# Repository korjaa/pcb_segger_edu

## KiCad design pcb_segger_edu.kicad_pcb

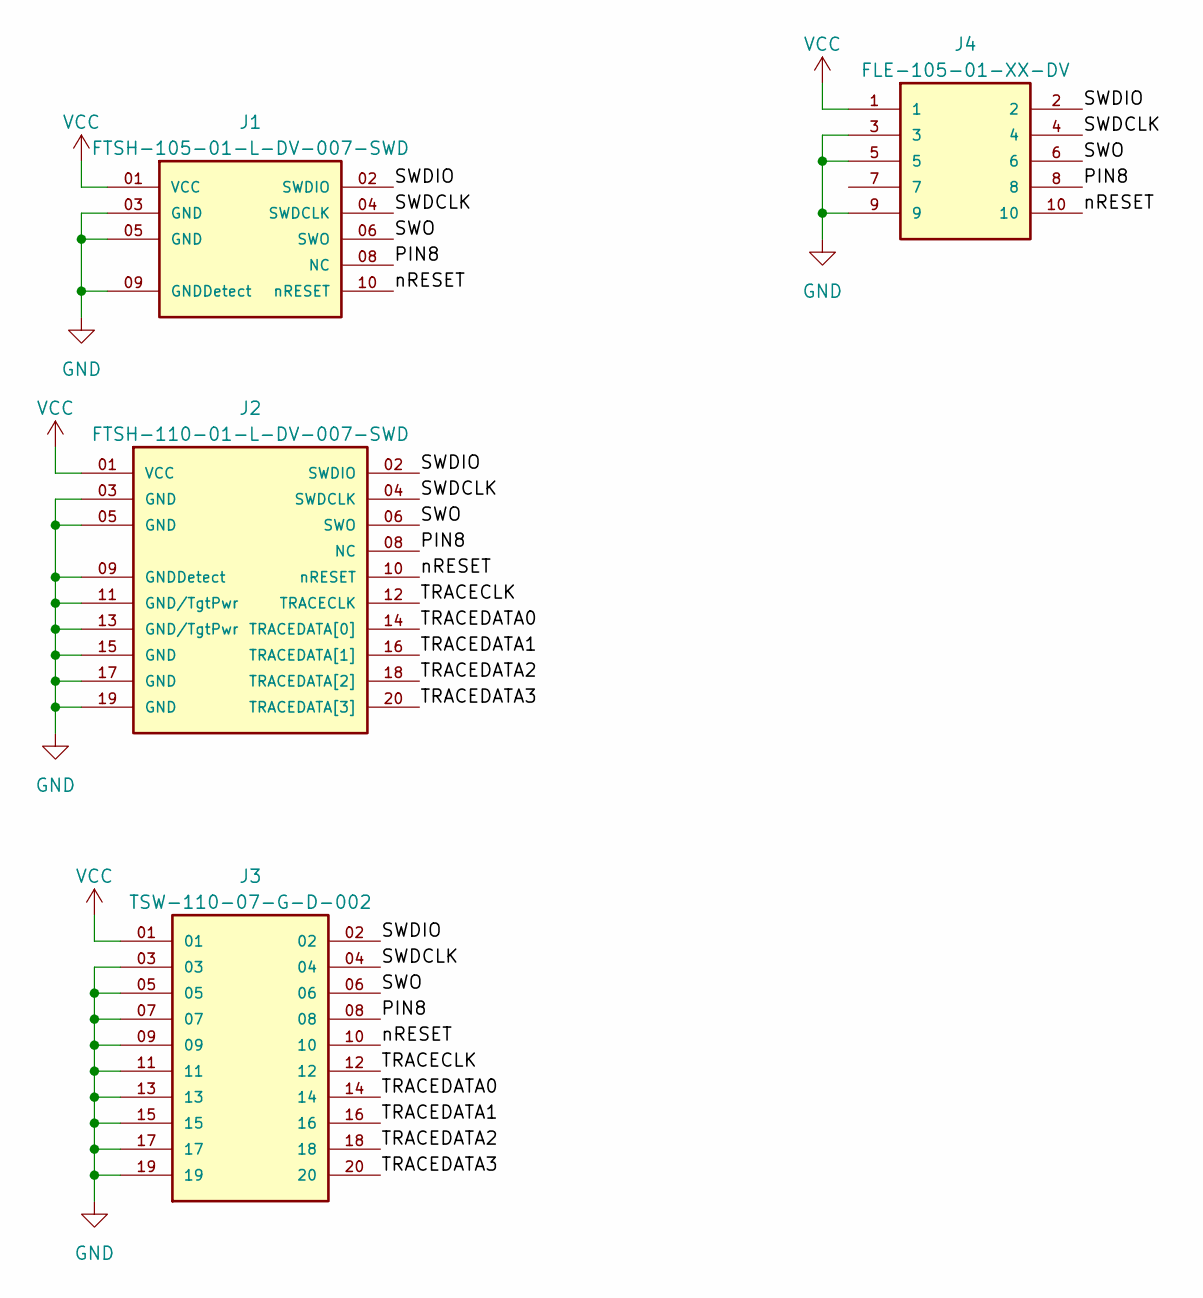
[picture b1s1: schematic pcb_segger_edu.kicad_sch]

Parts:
J1: FTSH-105-01-L-DV-007-SWD; FTSH-105-01-L-DV-007; PARTREV R
J2: FTSH-110-01-L-DV-007-SWD; FTSH-110-01-L-DV-007; PARTREV R
J3: TSW-110-07-G-D-002; PARTREV R
J4: FLE-105-01-XX-DV

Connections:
/PIN8: J1.08 (NC), J2.08 (NC), J3.08, J4.8
/SWDCLK: J1.04 (SWDCLK), J2.04 (SWDCLK), J3.04, J4.4
/SWDIO: J1.02 (SWDIO), J2.02 (SWDIO), J3.02, J4.2
/SWO: J1.06 (SWO), J2.06 (SWO), J3.06, J4.6
/TRACECLK: J2.12 (TRACECLK), J3.12
/TRACEDATA0: J2.14 (TRACEDATA[0]), J3.14
/TRACEDATA1: J2.16 (TRACEDATA[1]), J3.16
/TRACEDATA2: J2.18 (TRACEDATA[2]), J3.18
/TRACEDATA3: J2.20 (TRACEDATA[3]), J3.20
/nRESET: J1.10 (nRESET), J2.10 (nRESET), J3.10, J4.10
GND: J1.03 (GND), J1.05 (GND), J1.09 (GNDDetect), J2.03 (GND), J2.05 (GND), J2.09 (GNDDetect), J2.11 (GND/TgtPwr), J2.13 (GND/TgtPwr), J2.15 (GND), J2.17 (GND), J2.19 (GND), J3.03, J3.05, J3.07, J3.09, J3.11, J3.13, J3.15, J3.17, J3.19, J4.3, J4.5, J4.9
VCC: J1.01 (VCC), J2.01 (VCC), J3.01, J4.1

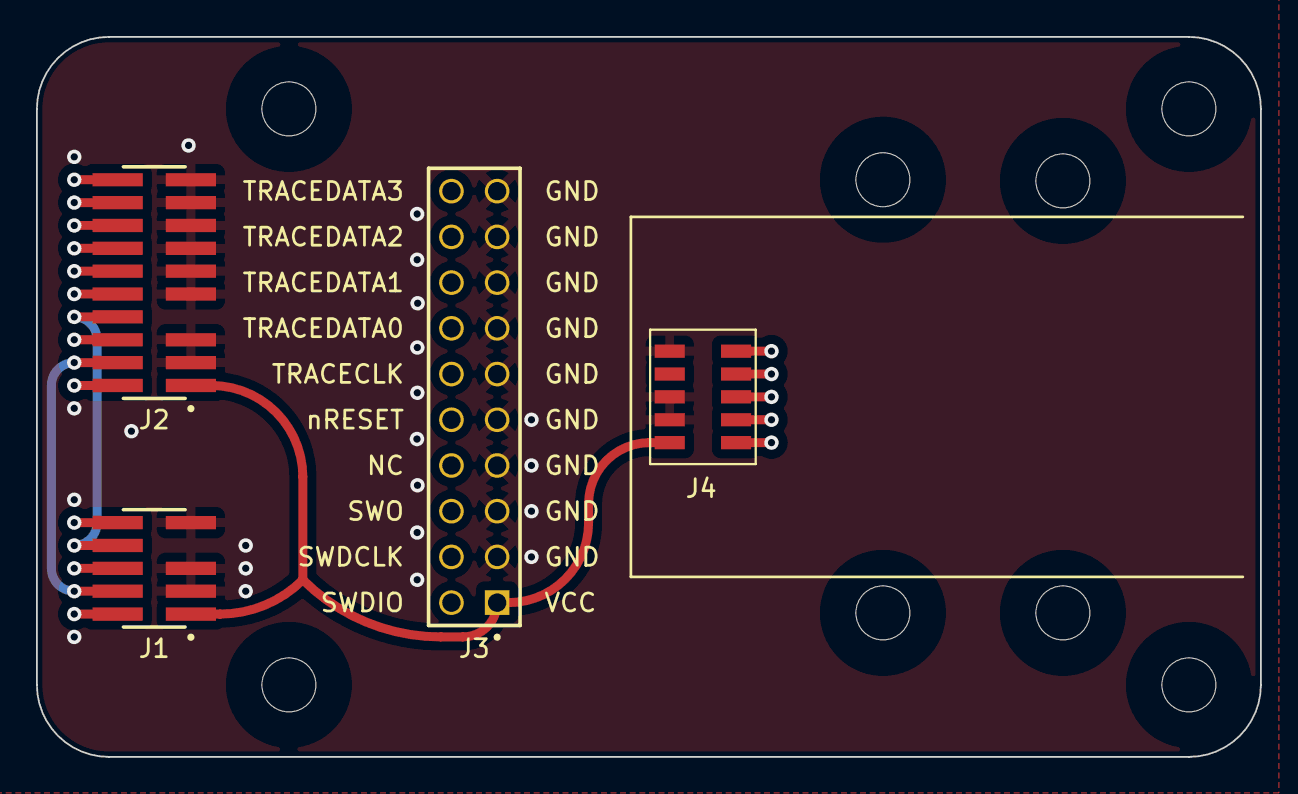
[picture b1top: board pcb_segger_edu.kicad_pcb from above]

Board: 4 copper layers, 68.0 x 40.0 mm, 4 parts (0 on the bottom side), 12 nets.

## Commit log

2023-06-11 Initial commit.
